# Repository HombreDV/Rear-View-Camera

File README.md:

# Rear-View-Camera
This will hold the work for rear view camera

WE tough like that 

Total Completion about 2%...

Thinking of using UART to send IR sensed voltage change to receiver, and have this value in a table in the reciever that will control a PWM sensor accordingly. (2/20/22)

SOW

System = Rear View Sensor

StackHolder Requirements:

- The System will be small enough to be held in your hands

- The system will work off of replacable batteries

- The system will communicate over bluetooth

- The system will notify User of proximity 

- The System will implement adjustable noises to User

- The System will have speaker for adjustable noises 

- The System will be portable

- The System will be water resistant

- The System will be Magnetic to stick on Vehicle Bumper

- The System will turn on using human capacitance ( Human Finger Sensing )

- The System will turn off using human capacitance

- The System will indicate when it is paired

- The system will remain paired until turned off

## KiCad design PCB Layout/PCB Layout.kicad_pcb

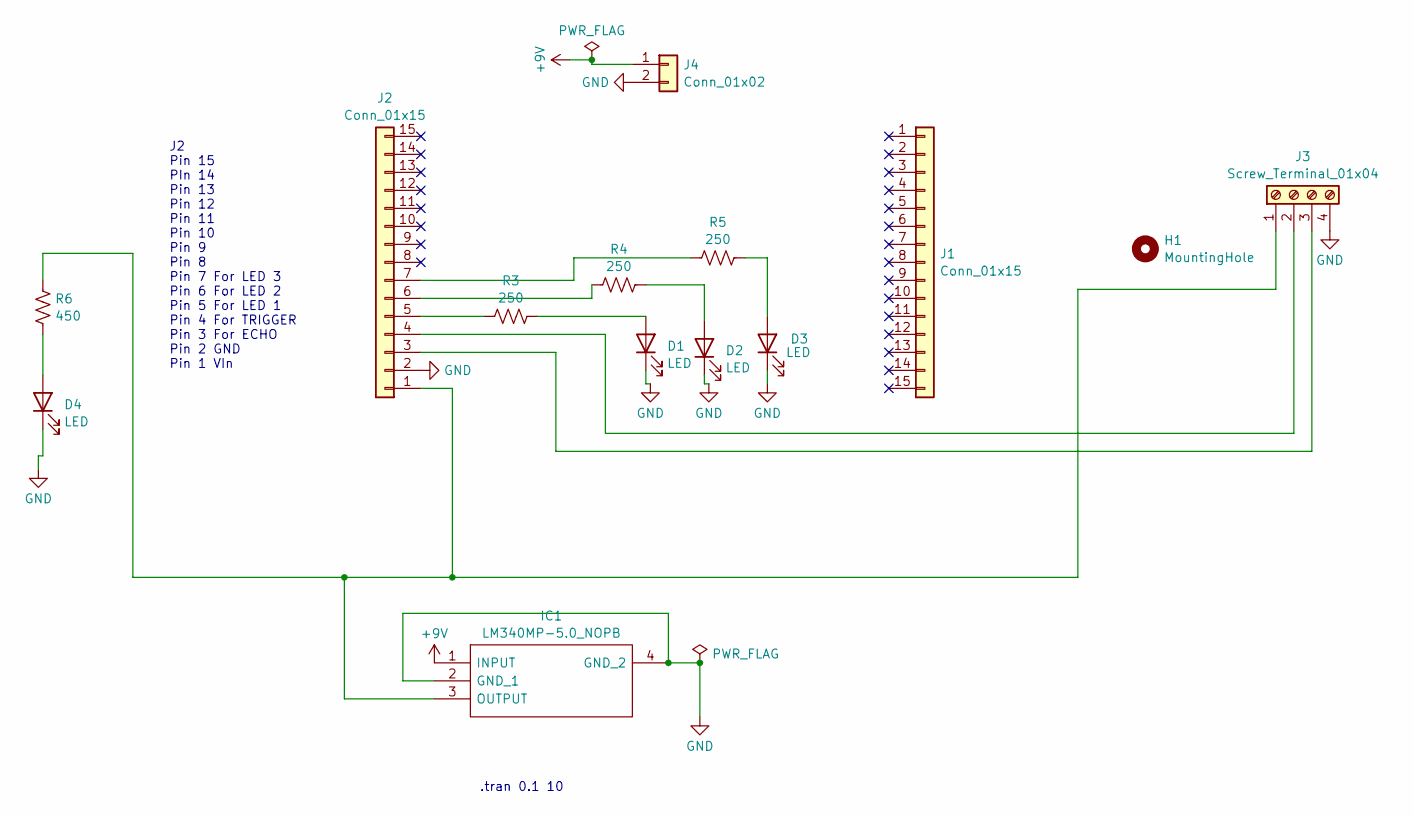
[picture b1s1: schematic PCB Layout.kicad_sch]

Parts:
D1, D2, D3, D4: LED; LED_1210_3225Metric_Pad1.42x2.65mm_HandSolder
H1: MountingHole; MountingHole_2.7mm_Pad
IC1: LM340MP-5.0_NOPB; SOT230P700X180-4N; Mouser Part Number 926-LM340MP-5.0/NOPB
J1, J2: Conn_01x15; PinSocket_1x15_P2.54mm_Vertical
J3: Screw_Terminal_01x04; PinSocket_1x04_P2.54mm_Vertical
J4: Conn_01x02; PinHeader_1x02_P2.54mm_Vertical
R3, R4, R5: 250; R_Axial_DIN0207_L6.3mm_D2.5mm_P7.62mm_Horizontal
R6: 450; R_Axial_DIN0207_L6.3mm_D2.5mm_P7.62mm_Horizontal

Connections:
+9V: IC1.1 (INPUT), J4.1
GND: D1.1 (K), D2.1 (K), D3.1 (K), D4.1 (K), IC1.2 (GND_1), IC1.4 (GND_2), J2.2, J3.4, J4.2
unnamed: D1.2 (A), R3.2
unnamed: D2.2 (A), R4.1
unnamed: D3.2 (A), R5.2
unnamed: D4.2 (A), R6.2
unnamed: IC1.3 (OUTPUT), J2.1, J3.1, R6.1
unnamed: J2.3, J3.3
unnamed: J2.4, J3.2
unnamed: J2.5, R3.1
unnamed: J2.6, R4.2
unnamed: J2.7, R5.1

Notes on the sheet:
J2 Pin 15 PIn 14 Pin 13 Pin 12 Pin 11 Pin 10 Pin 9 Pin 8 Pin 7 For LED 3 Pin 6 For LED 2 Pin 5 For LED 1 Pin 4 For TRIGGER Pin 3 For ECHO Pin 2 GND Pin 1 VIn
.tran 0.1 10

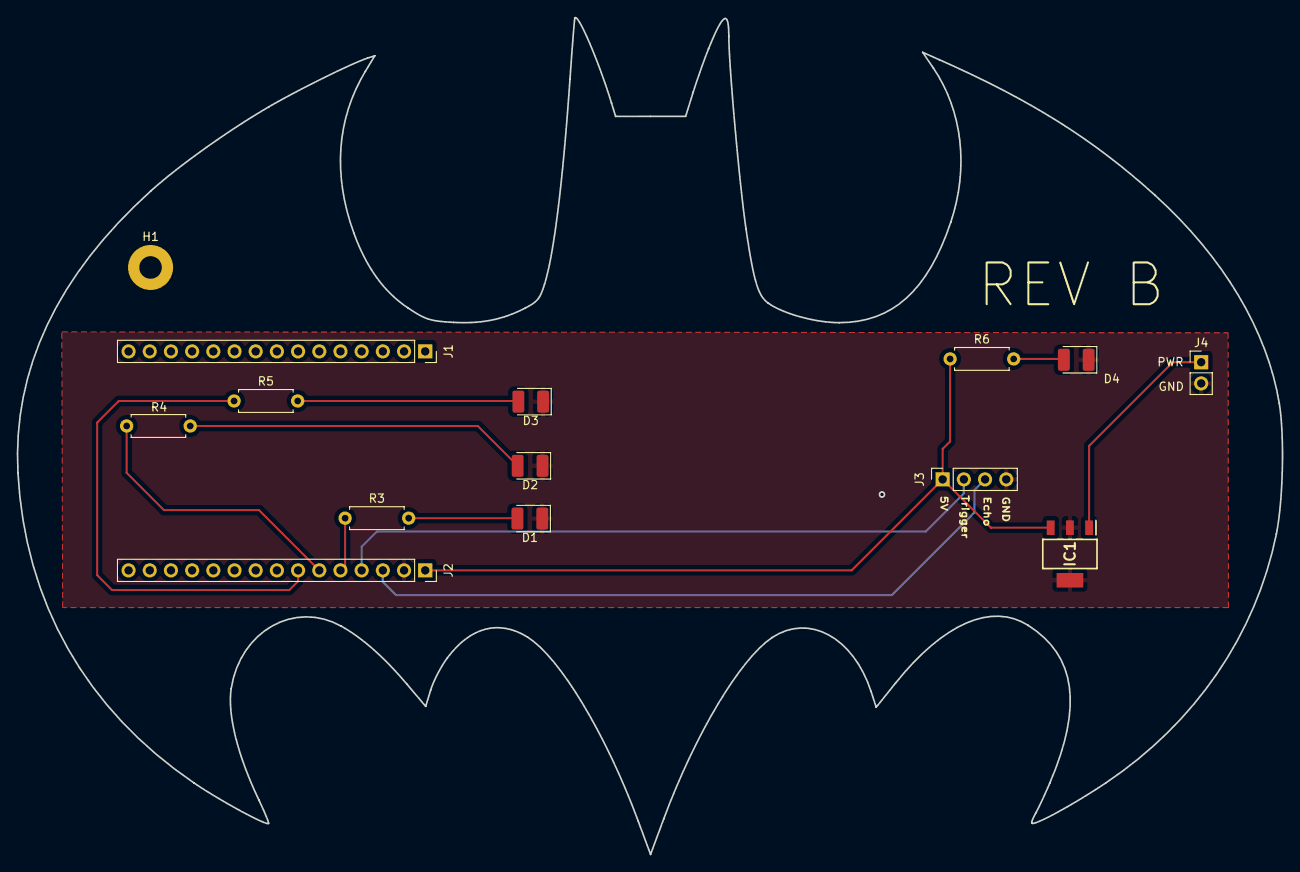
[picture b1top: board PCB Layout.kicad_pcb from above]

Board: 2 copper layers, 151.6 x 100.3 mm, 14 parts (0 on the bottom side), 12 nets.

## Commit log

2022-02-16 Here we go, Trying to achieve supersuper sayan
2022-02-16 Spec sheet for the Vatos
2022-02-17 The Requirements will be drafted once I have better idea of what I can possiblly use
2022-02-18 WiFi and Bluetooth Research
2022-02-21 General Purpose Input/output information
2022-02-24 Finished the ESP32 introduction and started a new resource to start downloading programing environment
2022-02-24 Added some requirements to Hardware, will need to review later once design constraints are better known
2022-03-04 Left off on the ESP32 install and need to view the initial blink Program
2022-03-29 More research on the ESP32, looks like I'll buy the DOIT DEV Kit. added aditional requirement breakdown
2022-04-07 added Stake Holder requirements, Will finalize requirements by EOW
2022-08-02 Changes for the risk Cube
2022-08-23 here we go
2022-08-23 wifi information was added
2022-08-24 Finished ESP32 video, research points to using BLE and touch sensitive pins
2022-12-30 the latest
2023-02-02 here is my latest work. added some changes to design and current requirement changes
2023-02-03 additional research on distance measurer
2023-09-24 Added PCB layout for the batlogo and any materials bought will later be added
2024-09-23 This increased the esp32 footprint to be spaced by 26.25 mm
2024-09-23 Getting the specs for the LM340 voltage regulator
